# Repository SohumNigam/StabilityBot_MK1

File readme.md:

# StabilityBot MK1

*Currently in prototype phase*

A self-balancing two-wheeled robot — an inverted pendulum stabilized
by IMU feedback and PID motor control, being built up toward full
4-state LQR control on a custom PCB.

**Full write-up / showcase:**
[sohumnigam.github.io/projects/stability_bot_MK1.html](https://sohumnigam.github.io/projects/stability_bot_MK1.html)

## Why I built this

I wanted a project that went past the usual "balance a robot with a
PID loop" hobby build — something that let me go deep on control
theory (state-space modeling, LQR, Kalman filtering), embedded
firmware, and PCB design all at once, and end up with a portfolio
piece that shows that depth rather than just a demo video. The
long-term goal is a robot that balances using a full 4-state LQR
controller (θ, θ̇, x, ẋ) on hardware I designed myself, with a
classical-vs-learned comparison against a reinforcement learning
controller down the line.

## Photos

## Demo Video

This version used PID to validate the hardware setup and learn about basic control theory. 

Will implement LQR in the future.

## Current Wiring Diagram (Subject to change)

## Future Diagram

## Current Features

- Active motor balancing response
- IMU sensor fusion (complementary filter, Kalman filter in progress)
- PID control loop
- Live web dashboard (WebSocket telemetry: pitch, motor output, PID
  tuning sliders) served from the ESP32 in SoftAP mode

## Hardware Overview

| Component | Current | Planned Upgrade |
|---|---|---|
| Compute | ESP32 Devboard | - |
| IMU | MPU6050 | Bosch BMI320 (SPI) |
| Motor driver | L293D | TB6612FNG |
| Motors | Standard yellow DC geared motors | — |
| Battery | ELEGOO battery pack | Will be compatible with any 2s Battery |
| Chassis | 3D printed | — |
| Encoders | None | AS5600 |

## Software Overview

**FreeRTOS control task**
- IMU readings
- PID calculations (LQR planned once encoders are integrated)
- Motor PWM control

**FreeRTOS web interface task**
- Digital logging
- Mobile control
- Remote PID tuning

## How to Assemble

<!-- TODO: fill in with real steps once chassis/wiring is finalized -->
1. 3D print the chassis (files: hardware/cad/step)
2. Mount motors and wheels using the screws that come with the yellow motors
3. Wire IMU, motor driver, and battery to the ESP32 per the defined pins in main.c (you will need to look in the motor structs for them)
4. Secure battery pack and IMU to minimize vibration noise. I used hot glue for this version.

## How to Flash

1. Clone this repo into your ESP-IDF project directory
2. Confirm your wiring matches the pin assignments in `main/`
3. Build and flash with `idf.py build flash monitor`
4. Connect to the robot's WebSocket dashboard to tune PID live

## Rough Bill of Materials

See the full BOM in BOM.csv. Still a work in progress as some passive parts are not yet finalized.

| Category | Qty | Part | Value | LCSC Part # | Price/unit | Extended Description | Link |
|---|---|---|---|---|---|---|---|
| Compute | 1 | ESP32 WROVER DevKitC | Espressif ESP32-WROVER-DevKitC | $11 | — | Purchased from DigiKey | [DigiKey](https://www.digikey.com/en/products/detail/espressif-systems/ESP32-DEVKITC-VIE/12091811) |
| IMU | 1 | BMI320 IMU | Bosch BMI320 | C22391148 | $0.99 | SPI IMU | [LCSC](https://www.lcsc.com/product-detail/C22391148.html) |
| Mechanics | 2 | Diametric Magnets | — | — | — | Will try to find (Hard to find affordable sources) | [Amazon](https://www.amazon.com/Diametrically-Magnetized-Neodymium-Permanent-Magnet/dp/B0GWXBS6SM) |
| Encoder | 1 | AS5600 Magnetic Encoder | AMS AS5600 | C499458 | $1.1855 | For wheel position tracking | [LCSC](https://www.lcsc.com/product-detail/C499458.html) |
| Motor Driver | 1 | TB6612FNG Motor Driver | Toshiba TB6612FNG | C141517 | $1.1659 | Target PCB driver; STBY tied to GPIO | [LCSC](https://www.lcsc.com/product-detail/C141517.html) |
| Mechanical | 2 | DC Gear Motors | — | $20 | — | Includes wheels | [Amazon](https://www.amazon.ca/SazkJere-Geared-Motor-Gearbox-200RPM/dp/B0G64KFYPS) |
| Mechanical | 1 | Chassis / Frame (custom) | — | — | — | Onshape CAD; STEP in `hardware/cad/step/` | — |

Full robot rough cost ~$170 + shipping

## Known Issues

- IMU signal occasionally drops out on the current breadboard
  prototype — traced to noise from jumper wire connections; largely
  mitigated with twisted GND pairs and a control-loop delay, but not
  fully eliminated. Root fix is the move to a soldered BMI320 board
  and eventually the custom PCB.
- 4-state LQR not yet running on hardware — pending encoder
  integration.

## Credits

- Built on [ESP-IDF](https://github.com/espressif/esp-idf) (Espressif)

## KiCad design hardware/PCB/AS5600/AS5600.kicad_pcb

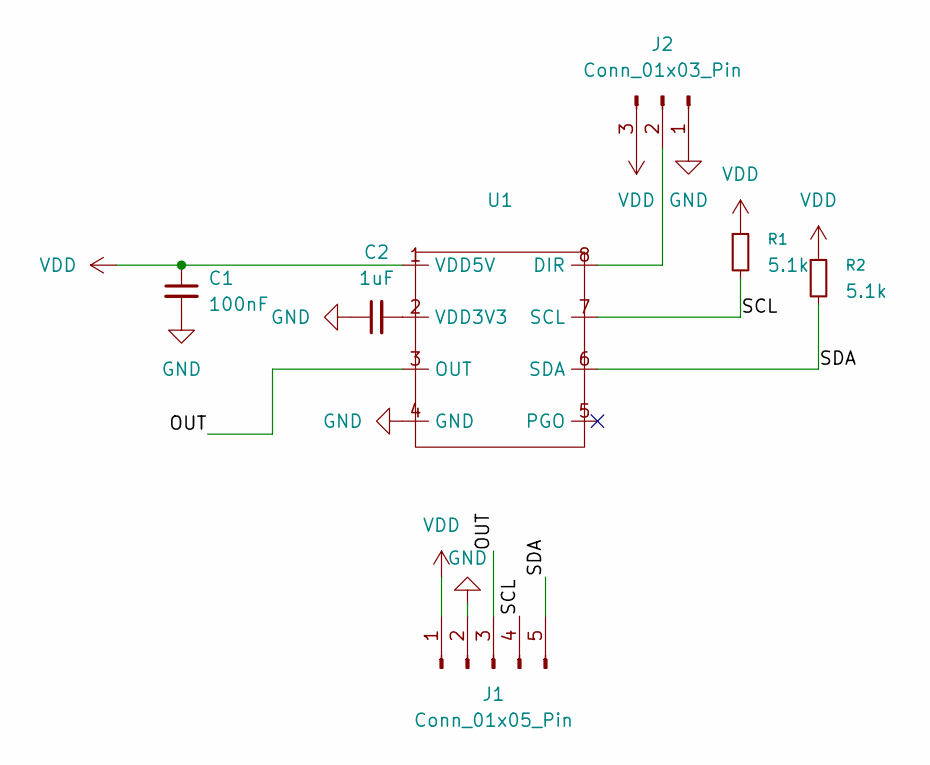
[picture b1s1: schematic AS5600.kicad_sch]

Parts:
C1: 100nF; C_0805_2012Metric_Pad1.18x1.45mm_HandSolder
C2: 1uF; C_0805_2012Metric_Pad1.18x1.45mm_HandSolder
J1: Conn_01x05_Pin; PinSocket_1x05_P2.54mm_Vertical
J2: Conn_01x03_Pin; SolderJumper-3_P1.3mm_Bridged12_RoundedPad1.0x1.5mm
R1, R2: 5.1k; R_0603_1608Metric_Pad0.98x0.95mm_HandSolder
U1: SOIC-8_3.9x4.9mm_P1.27mm

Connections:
/OUT: J1.3, U1.3 (OUT)
/SCL: J1.4, R1.2, U1.7 (SCL)
/SDA: J1.5, R2.2, U1.6 (SDA)
GND: C1.2, C2.1, J1.2, J2.1, U1.4 (GND)
unnamed: J2.2, U1.8 (DIR)
unnamed: C2.2, U1.2 (VDD3V3)
VDD: C1.1, J1.1, J2.3, R1.1, R2.1, U1.1 (VDD5V)

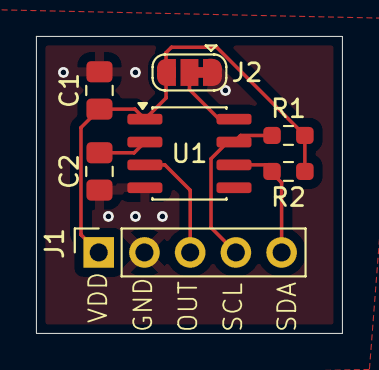
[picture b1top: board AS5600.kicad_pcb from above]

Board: 2 copper layers, 17.0 x 16.5 mm, 7 parts (0 on the bottom side), 7 nets.

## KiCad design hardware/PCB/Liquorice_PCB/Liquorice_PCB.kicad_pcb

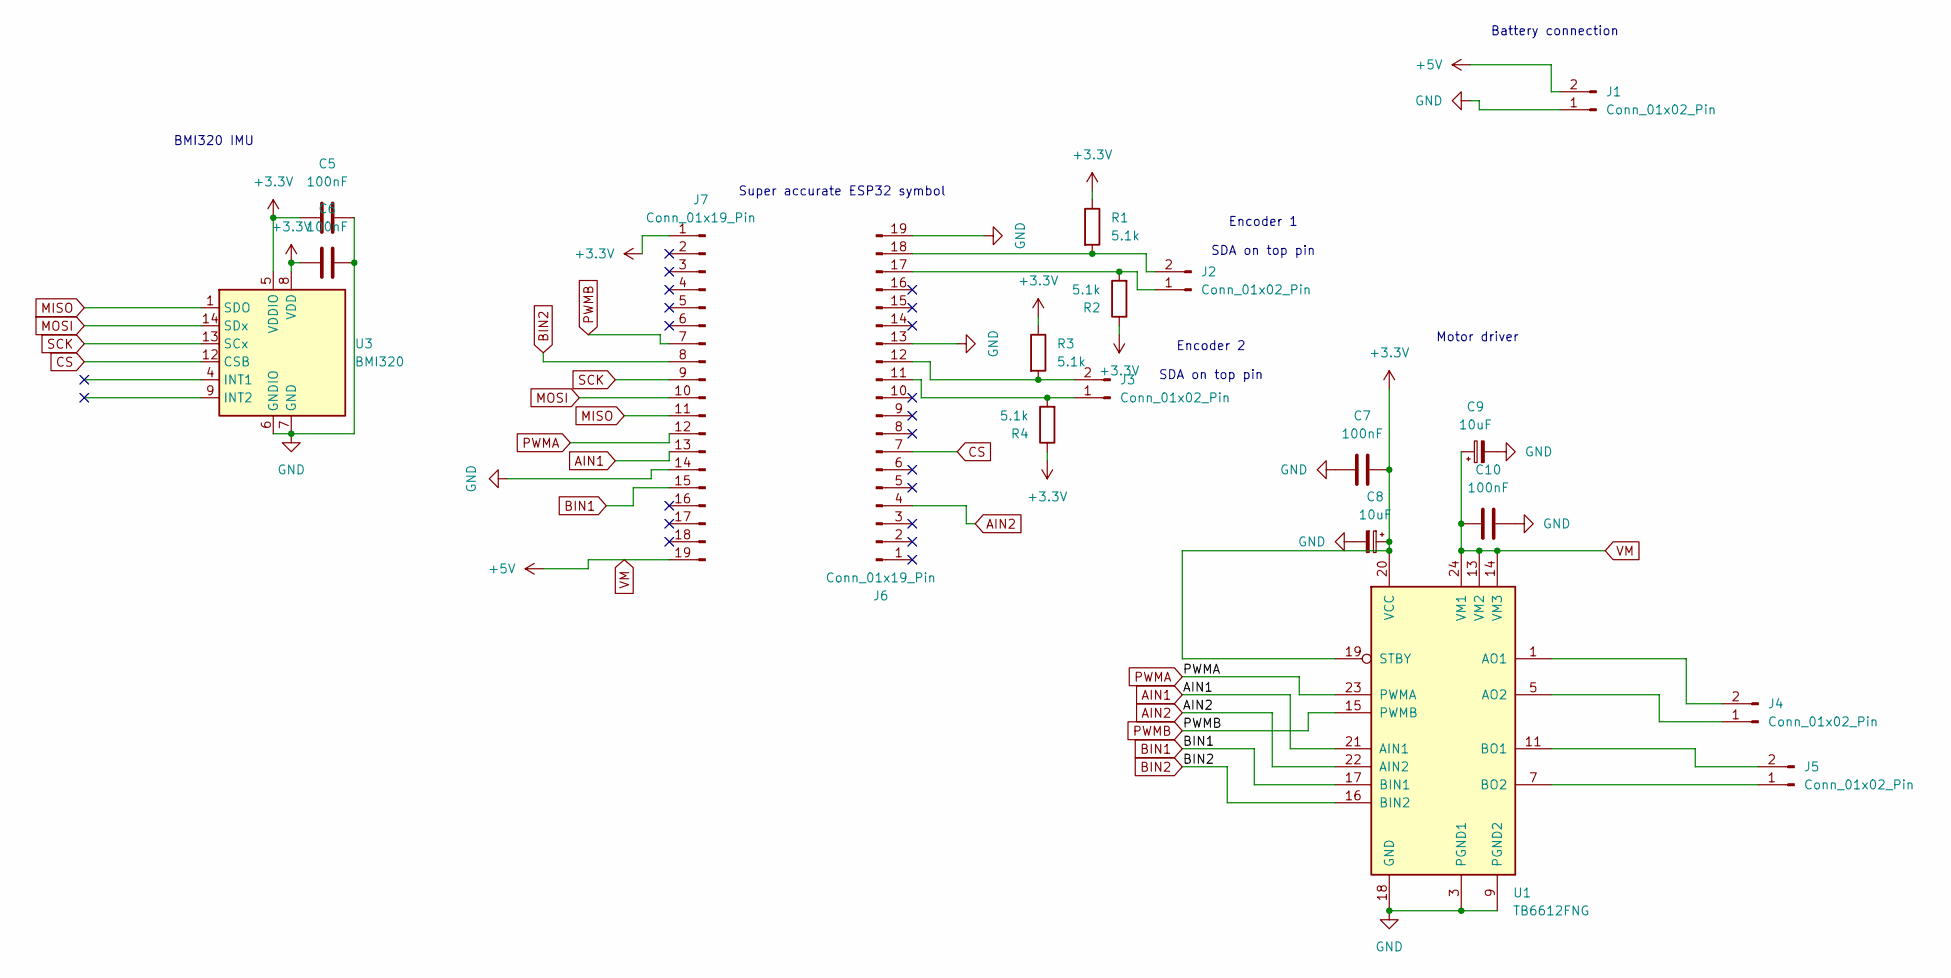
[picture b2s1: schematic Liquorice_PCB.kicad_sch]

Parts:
C5, C6, C7, C10: 100nF; C_0805_2012Metric_Pad1.18x1.45mm_HandSolder
C8, C9: 10uF; CP_EIA-3216-18_Kemet-A_HandSolder
J1, J2, J3, J4, J5: Conn_01x02_Pin; PinHeader_1x02_P2.54mm_Vertical
J6, J7: Conn_01x19_Pin; PinHeader_1x19_P2.54mm_Vertical
R1, R2, R3, R4: 5.1k; R_0603_1608Metric_Pad0.98x0.95mm_HandSolder
U1: TB6612FNG; SSOP-24_5.3x8.2mm_P0.65mm
U3: BMI320; Bosch_LGA-14_3x2.5mm_P0.5mm

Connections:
+3.3V: C5.1, C6.1, C7.2, C8.1, J7.1, R1.1, R2.1, R3.1, R4.1, U1.19 (STBY), U1.20 (VCC), U3.5 (VDDIO), U3.8 (VDD)
AIN1: J7.13, U1.21 (AIN1)
AIN2: J6.4, U1.22 (AIN2)
BIN1: J7.15, U1.17 (BIN1)
BIN2: J7.8, U1.16 (BIN2)
CS: J6.7, U3.12 (CSB)
GND: C5.2, C6.2, C7.1, C8.2, C9.2, C10.2, J1.1, J6.13, J6.19, J7.14, U1.3 (PGND1), U1.4 (PGND1), U1.9 (PGND2), U1.10 (PGND2), U1.18 (GND), U3.6 (GNDIO), U3.7 (GND)
MISO: J7.11, U3.1 (SDO)
MOSI: J7.10, U3.14 (SDx)
unnamed: J2.1, J6.17, R2.2
unnamed: J2.2, J6.18, R1.2
unnamed: J3.1, J6.11, R4.2
unnamed: J3.2, J6.12, R3.2
unnamed: J4.1, U1.5 (AO2), U1.6 (AO2)
unnamed: J4.2, U1.1 (AO1), U1.2 (AO1)
unnamed: J5.1, U1.7 (BO2), U1.8 (BO2)
unnamed: J5.2, U1.11 (BO1), U1.12 (BO1)
PWMA: J7.12, U1.23 (PWMA)
PWMB: J7.7, U1.15 (PWMB)
SCK: J7.9, U3.13 (SCx)
VM: C9.1, C10.1, J1.2, J7.19, U1.13 (VM2), U1.14 (VM3), U1.24 (VM1)

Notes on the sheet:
Encoder 1 SDA on top pin
Motor driver
BMI320 IMU
Super accurate ESP32 symbol
Battery connection
Encoder 2 SDA on top pin

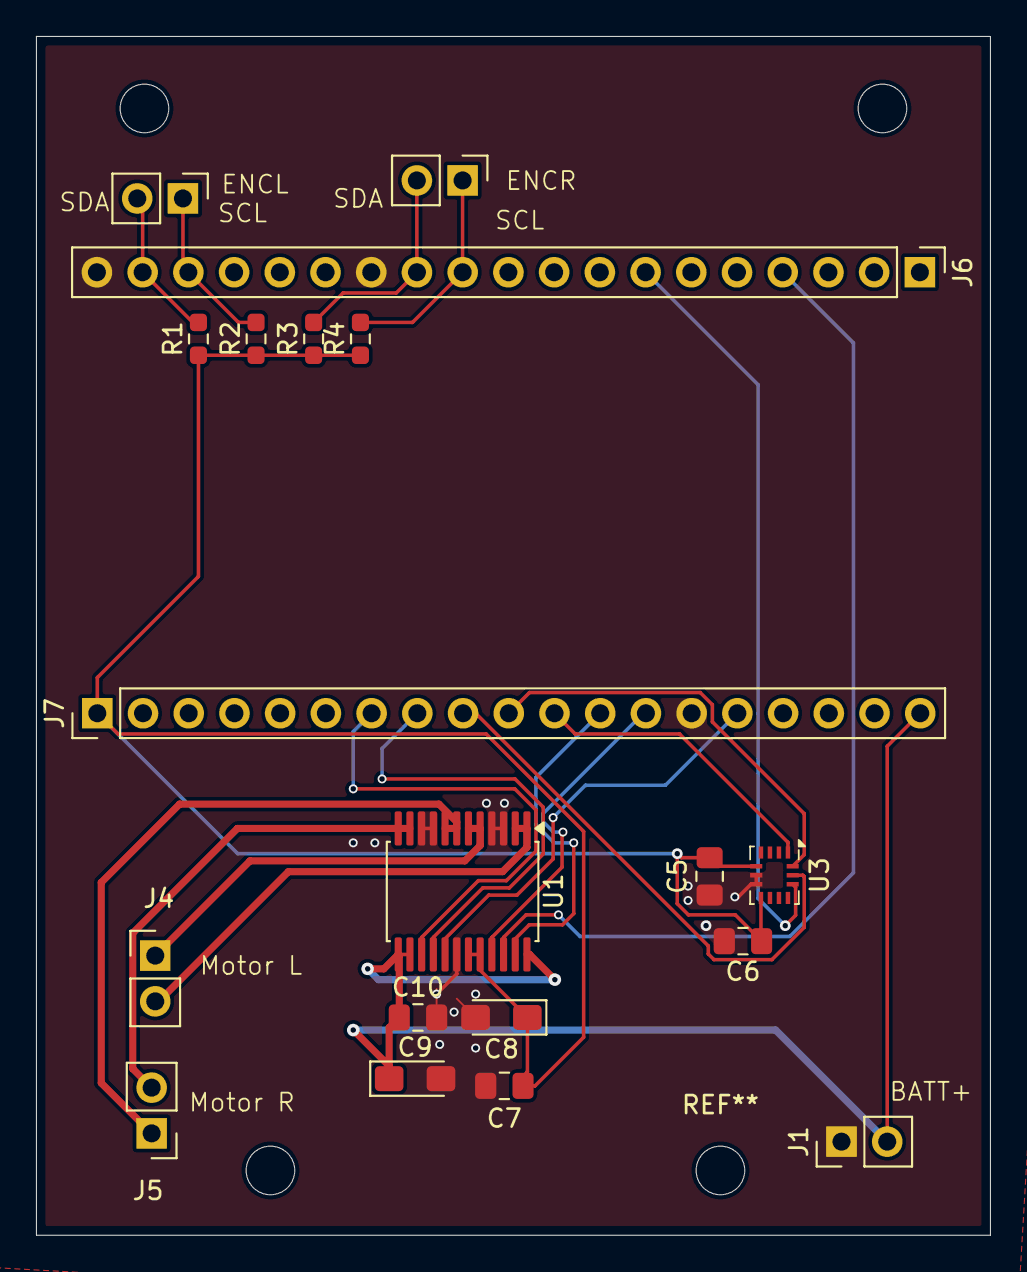
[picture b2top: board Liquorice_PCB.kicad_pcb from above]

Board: 2 copper layers, 53.0 x 66.6 mm, 19 parts (0 on the bottom side), 21 nets.

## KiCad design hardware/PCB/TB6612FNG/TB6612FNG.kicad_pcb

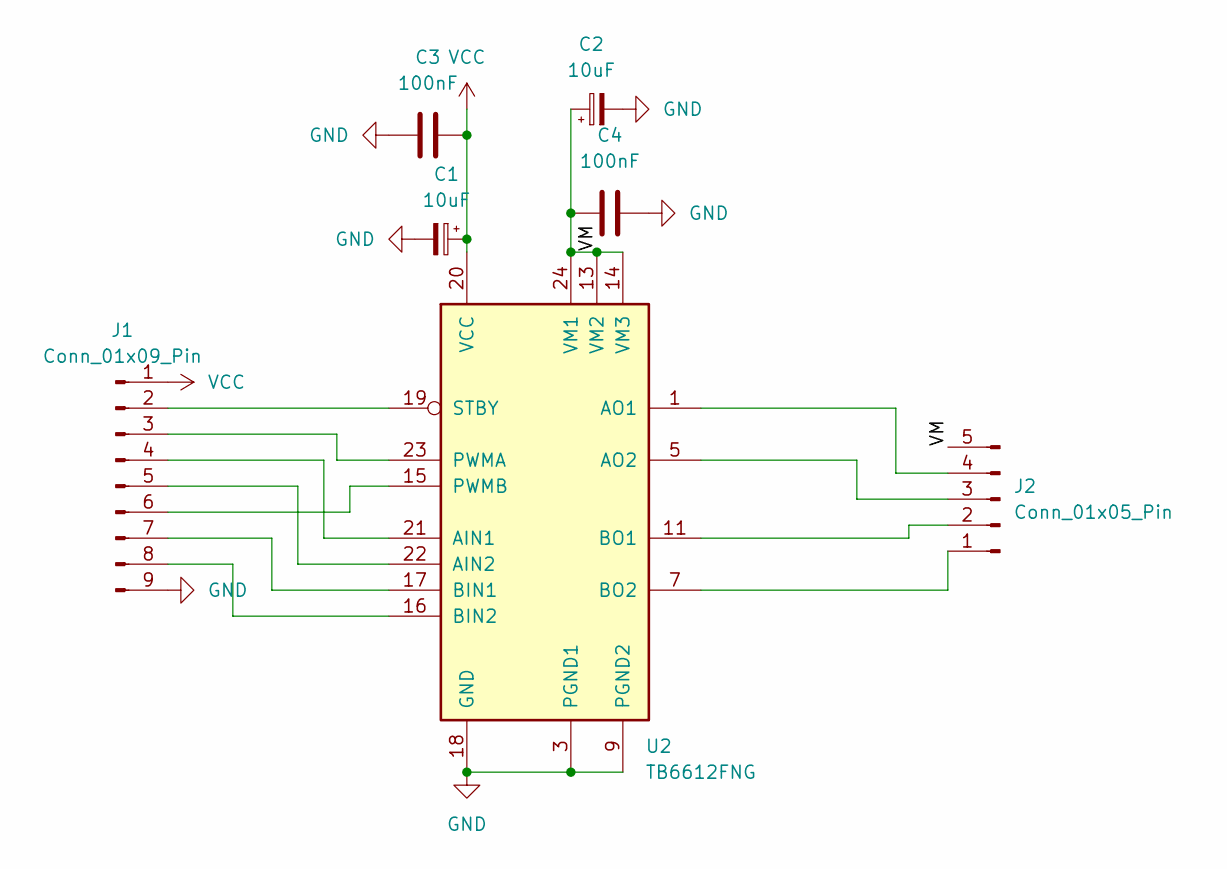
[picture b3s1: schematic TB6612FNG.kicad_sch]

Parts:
C1, C2: 10uF; CP_EIA-3216-18_Kemet-A_HandSolder
C3, C4: 100nF; C_0805_2012Metric_Pad1.18x1.45mm_HandSolder
J1: Conn_01x09_Pin; PinSocket_1x09_P2.54mm_Vertical
J2: Conn_01x05_Pin; PinSocket_1x05_P2.54mm_Vertical
U2: TB6612FNG; SSOP-24_5.3x8.2mm_P0.65mm

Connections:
/VM: C2.1, C4.1, J2.5, U2.13 (VM2), U2.14 (VM3), U2.24 (VM1)
GND: C1.2, C2.2, C3.1, C4.2, J1.9, U2.3 (PGND1), U2.4 (PGND1), U2.9 (PGND2), U2.10 (PGND2), U2.18 (GND)
unnamed: J1.2, U2.19 (STBY)
unnamed: J1.3, U2.23 (PWMA)
unnamed: J1.4, U2.21 (AIN1)
unnamed: J1.5, U2.22 (AIN2)
unnamed: J1.6, U2.15 (PWMB)
unnamed: J1.7, U2.17 (BIN1)
unnamed: J1.8, U2.16 (BIN2)
unnamed: J2.1, U2.7 (BO2), U2.8 (BO2)
unnamed: J2.2, U2.11 (BO1), U2.12 (BO1)
unnamed: J2.3, U2.5 (AO2), U2.6 (AO2)
unnamed: J2.4, U2.1 (AO1), U2.2 (AO1)
VCC: C1.1, C3.2, J1.1, U2.20 (VCC)

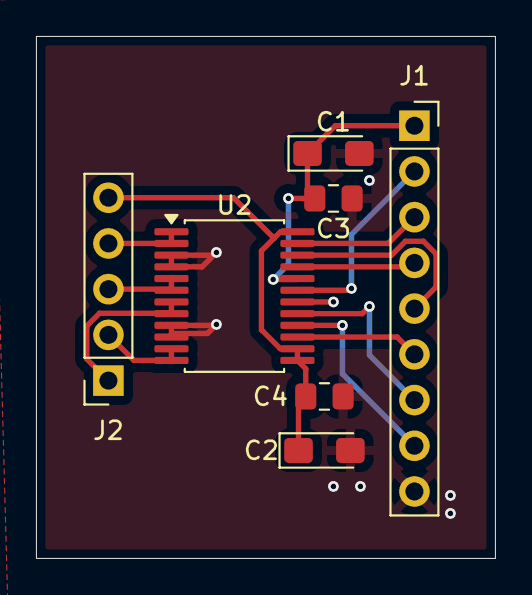
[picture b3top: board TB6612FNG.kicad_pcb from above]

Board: 2 copper layers, 25.5 x 29.0 mm, 7 parts (0 on the bottom side), 14 nets.

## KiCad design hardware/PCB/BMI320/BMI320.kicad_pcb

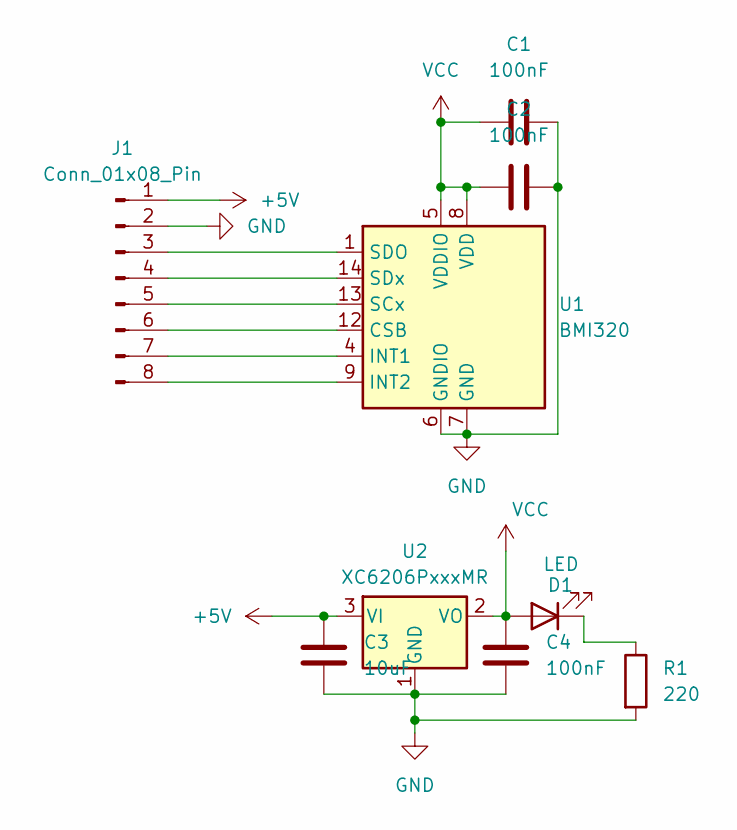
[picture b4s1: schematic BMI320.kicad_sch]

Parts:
C1, C2, C4: 100nF; C_0805_2012Metric_Pad1.18x1.45mm_HandSolder
C3: 10uF; C_0805_2012Metric_Pad1.18x1.45mm_HandSolder
D1: LED; LED_0603_1608Metric_Pad1.05x0.95mm_HandSolder
J1: Conn_01x08_Pin; PinHeader_1x08_P2.54mm_Vertical
R1: 220; R_0603_1608Metric_Pad0.98x0.95mm_HandSolder
U1: BMI320; Bosch_LGA-14_3x2.5mm_P0.5mm
U2: XC6206PxxxMR; SOT-23-3

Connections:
+5V: C3.2, J1.1, U2.3 (VI)
GND: C1.2, C2.2, C3.1, C4.1, J1.2, R1.2, U1.6 (GNDIO), U1.7 (GND), U2.1 (GND)
unnamed: D1.1 (K), R1.1
unnamed: J1.3, U1.1 (SDO)
unnamed: J1.4, U1.14 (SDx)
unnamed: J1.5, U1.13 (SCx)
unnamed: J1.6, U1.12 (CSB)
unnamed: J1.7, U1.4 (INT1)
unnamed: J1.8, U1.9 (INT2)
VCC: C1.1, C2.1, C4.2, D1.2 (A), U1.5 (VDDIO), U1.8 (VDD), U2.2 (VO)

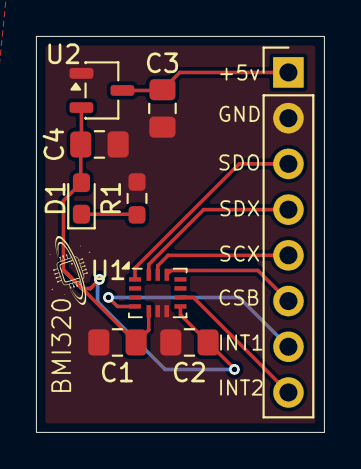
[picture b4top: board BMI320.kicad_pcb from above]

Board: 2 copper layers, 16.0 x 22.0 mm, 9 parts (0 on the bottom side), 10 nets.

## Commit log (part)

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2026-06-01 initial commit with IMU proof of concept
2026-06-21 initial testing setup
